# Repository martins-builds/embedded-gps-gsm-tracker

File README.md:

# embedded-gps-gsm-tracker
Custom GPS/GSM embedded tracking system with custom PCB, firmware, OLED display, and Web dashboard

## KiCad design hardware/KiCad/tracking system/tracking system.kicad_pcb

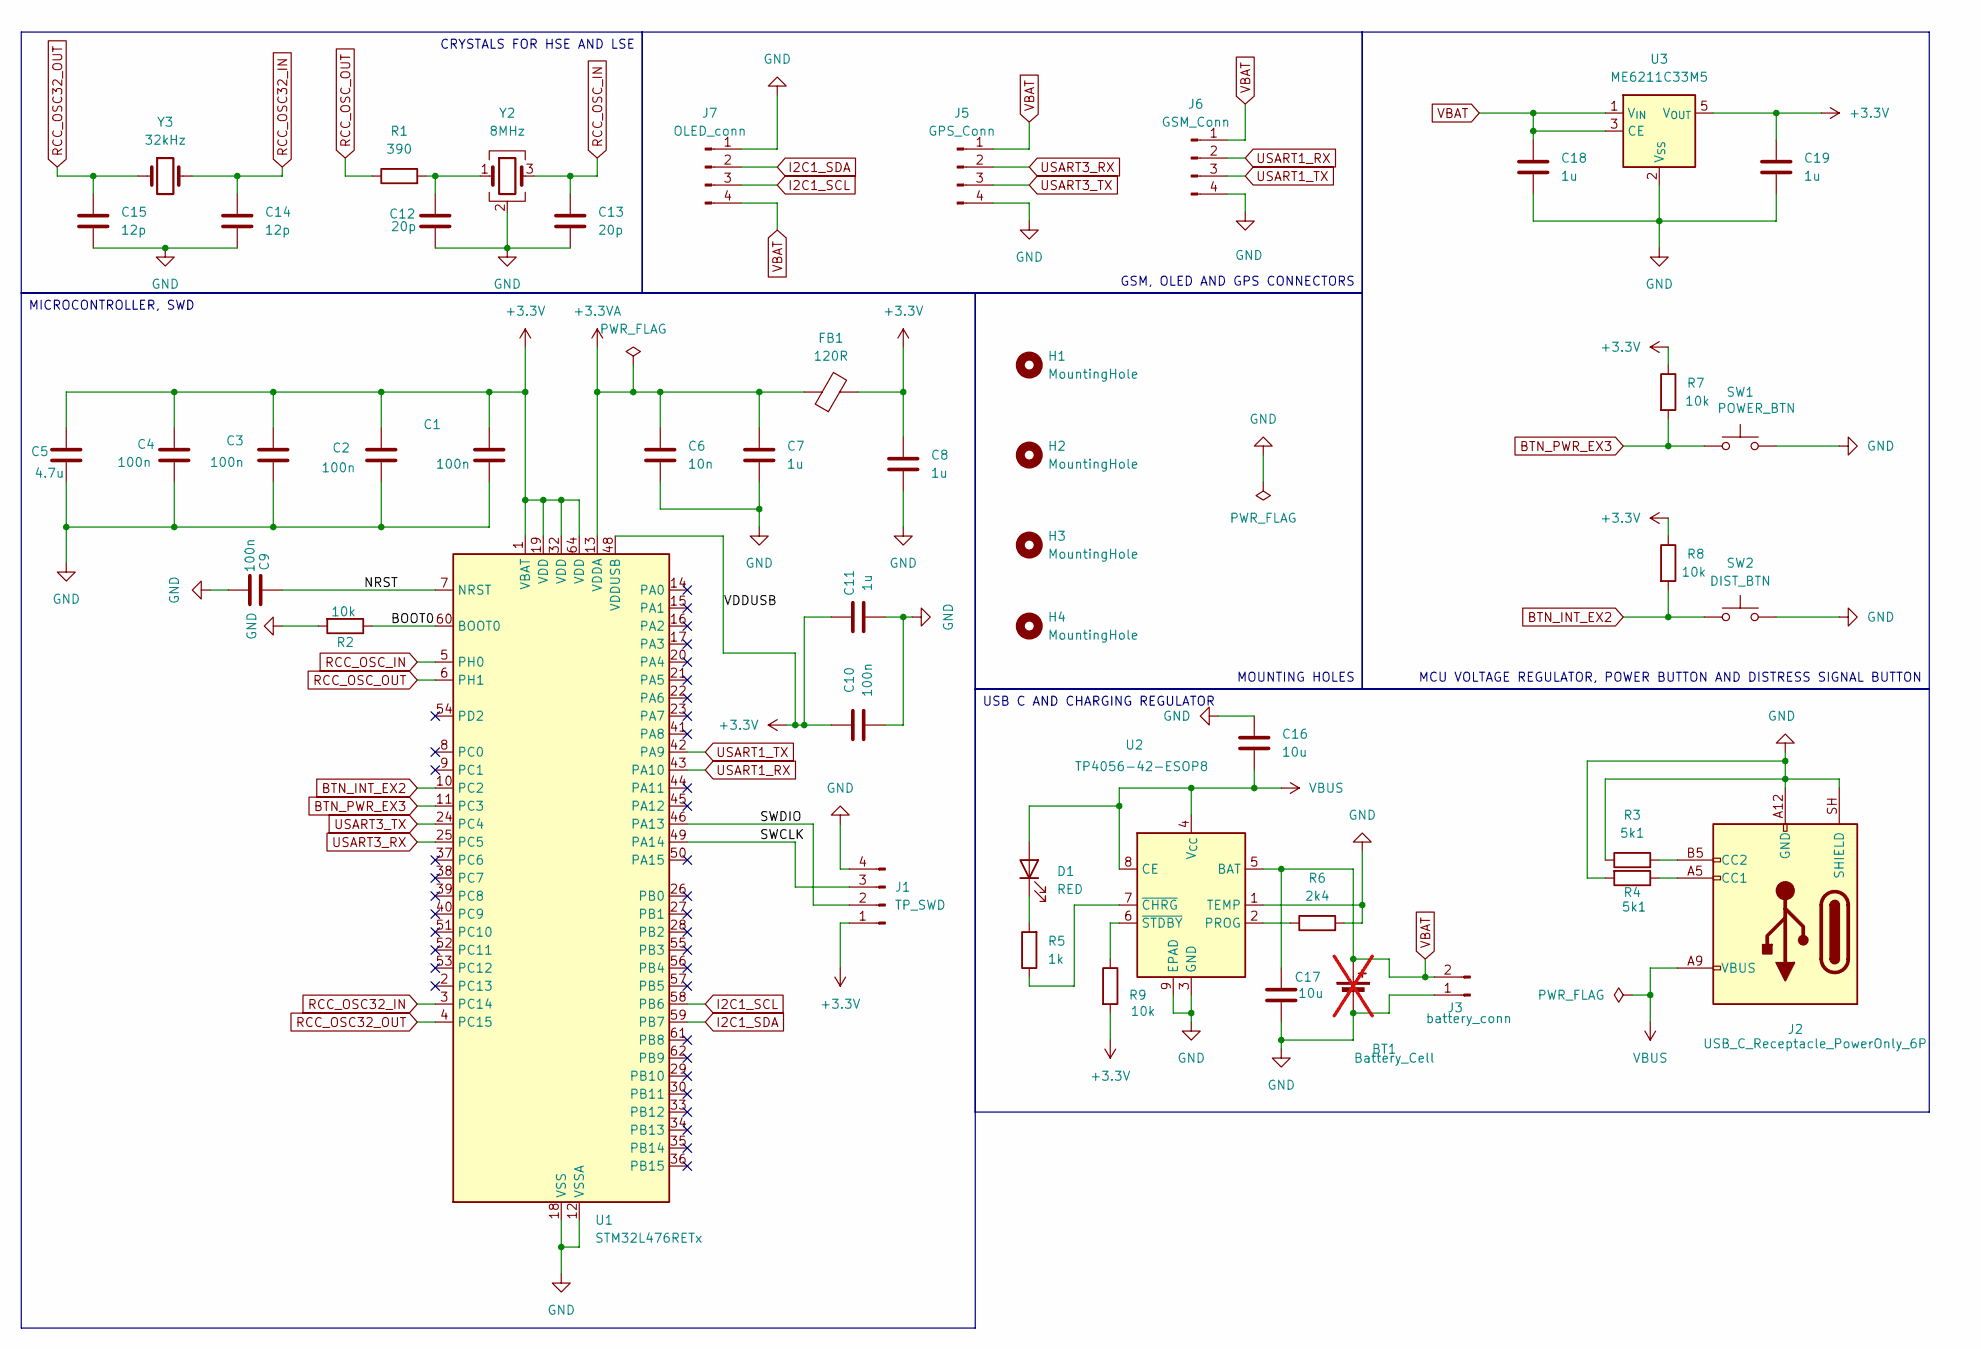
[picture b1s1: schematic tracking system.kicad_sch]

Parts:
BT1: Battery_Cell; not fitted
C1, C2, C3, C4, C9, C10: 100n; C_0402_1005Metric
C5: 4.7u; C_0402_1005Metric
C6: 10n; C_0402_1005Metric
C7, C8, C11, C18, C19: 1u; C_0402_1005Metric
C12, C13: 20p; C_0402_1005Metric
C14, C15: 12p; C_0402_1005Metric
C16, C17: 10u; C_0603_1608Metric
D1: RED; LED_0603_1608Metric
FB1: 120R; L_0603_1608Metric
H1, H2, H3, H4: MountingHole; MountingHole_3.2mm_M3_DIN965_Pad
J1: TP_SWD; PinHeader_1x04_P2.54mm_Vertical
J2: USB_C_Receptacle_PowerOnly_6P; USB_C_Receptacle_GCT_USB4125-xx-x_6P_TopMnt_Horizontal
J3: battery_conn; PinHeader_1x02_P2.54mm_Vertical
J5: GPS_Conn; PinHeader_1x04_P2.54mm_Vertical
J6: GSM_Conn; PinHeader_1x04_P2.54mm_Vertical
J7: OLED_conn; PinHeader_1x04_P2.54mm_Vertical
R1: 390; R_0402_1005Metric
R2, R7, R8, R9: 10k; R_0402_1005Metric
R3, R4: 5k1; R_0402_1005Metric
R5: 1k; R_0402_1005Metric
R6: 2k4; R_0402_1005Metric
SW1: POWER_BTN; SW_Push_1P1T_NO_CK_KMR2
SW2: DIST_BTN; SW_Push_1P1T_NO_CK_KMR2
U1: STM32L476RETx; LQFP-64_10x10mm_P0.5mm
U2: TP4056-42-ESOP8; SOIC-8-1EP_3.9x4.9mm_P1.27mm_EP2.29x3mm
U3: ME6211C33M5; SOT-23-5
Y2: 8MHz; Crystal_SMD_3225-4Pin_3.2x2.5mm
Y3: 32kHz; Crystal_SMD_3215-2Pin_3.2x1.5mm

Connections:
+3.3V: C1.1, C2.2, C3.2, C4.1, C5.2, C8.1, C10.1, C11.1, C19.1, FB1.2, J1.1, R7.1, R8.1, R9.2, U1.1 (VBAT), U1.19 (VDD), U1.32 (VDD), U1.48 (VDDUSB), U1.64 (VDD), U3.5 (V_{OUT})
+3.3VA: C6.1, C7.1, FB1.1, U1.13 (VDDA)
/BOOT0: R2.1, U1.60 (BOOT0)
/NRST: C9.1, U1.7 (NRST)
/SWCLK: J1.3, U1.49 (PA14)
/SWDIO: J1.2, U1.46 (PA13)
BTN_INT_EX2: R8.2, SW2.1, U1.10 (PC2)
BTN_PWR_EX3: R7.2, SW1.1, U1.11 (PC3)
GND: BT1.2 (-), C1.2, C2.1, C3.1, C4.2, C5.1, C6.2, C7.2, C8.2, C9.2, C10.2, C11.2, C12.2, C13.2, C14.2, C15.2, C16.1, C17.2, C18.2, C19.2, J1.4, J2.A12 (GND), J2.B12 (GND), J2.SH (SHIELD), J3.1, J5.4, J6.4, J7.1, R2.2, R3.1, R4.2, R6.2, SW1.2, SW2.2, U1.12 (VSSA), U1.18 (VSS), U1.31 (VSS), U1.47 (VSS), U1.63 (VSS), U2.1 (TEMP), U2.3 (GND), U2.9 (EPAD), U3.2 (V_{SS}), Y2.2 (G), Y2.4 (G)
I2C1_SCL: J7.3, U1.58 (PB6)
I2C1_SDA: J7.2, U1.59 (PB7)
unnamed: C12.1, R1.2, Y2.1
unnamed: D1.1 (K), R5.2
unnamed: J2.A5 (CC1), R4.1
unnamed: J2.B5 (CC2), R3.2
unnamed: R6.1, U2.2 (PROG)
unnamed: R5.1, U2.7 (~CHRG)
unnamed: R9.1, U2.6 (~STDBY)
RCC_OSC32_IN: C14.1, U1.3 (PC14), Y3.2
RCC_OSC32_OUT: C15.1, U1.4 (PC15), Y3.1
RCC_OSC_IN: C13.1, U1.5 (PH0), Y2.3
RCC_OSC_OUT: R1.1, U1.6 (PH1)
USART1_RX: J6.2, U1.43 (PA10)
USART1_TX: J6.3, U1.42 (PA9)
USART3_RX: J5.2, U1.25 (PC5)
USART3_TX: J5.3, U1.24 (PC4)
VBAT: BT1.1 (+), C17.1, C18.1, J3.2, J5.1, J6.1, J7.4, U2.5 (BAT), U3.1 (V_{IN}), U3.3 (CE)
VBUS: C16.2, D1.2 (A), J2.A9 (VBUS), J2.B9 (VBUS), U2.4 (V_{CC}), U2.8 (CE)

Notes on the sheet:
CRYSTALS FOR HSE AND LSE
USB C AND CHARGING REGULATOR
GSM, OLED AND GPS CONNECTORS
MOUNTING HOLES
MCU VOLTAGE REGULATOR, POWER BUTTON AND DISTRESS SIGNAL BUTTON
MICROCONTROLLER, SWD

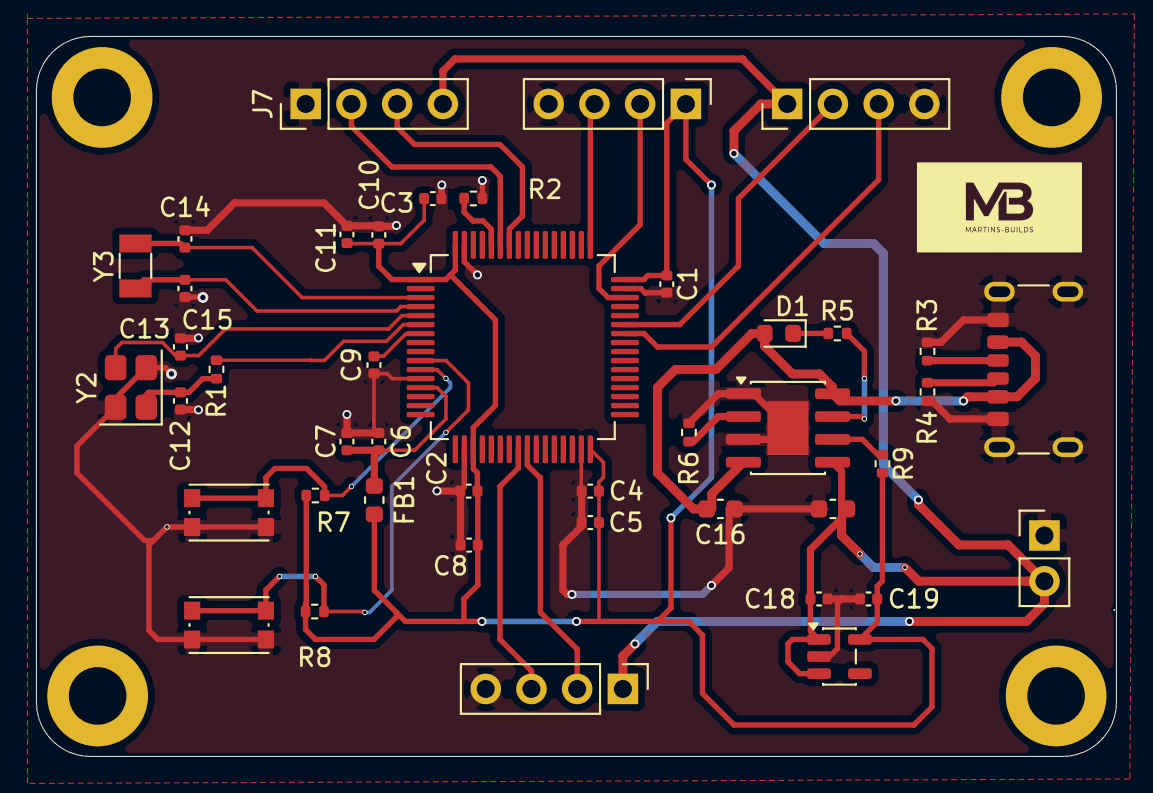
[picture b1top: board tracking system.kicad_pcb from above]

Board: 2 copper layers, 60.0 x 40.0 mm, 47 parts (0 on the bottom side), 28 nets.
